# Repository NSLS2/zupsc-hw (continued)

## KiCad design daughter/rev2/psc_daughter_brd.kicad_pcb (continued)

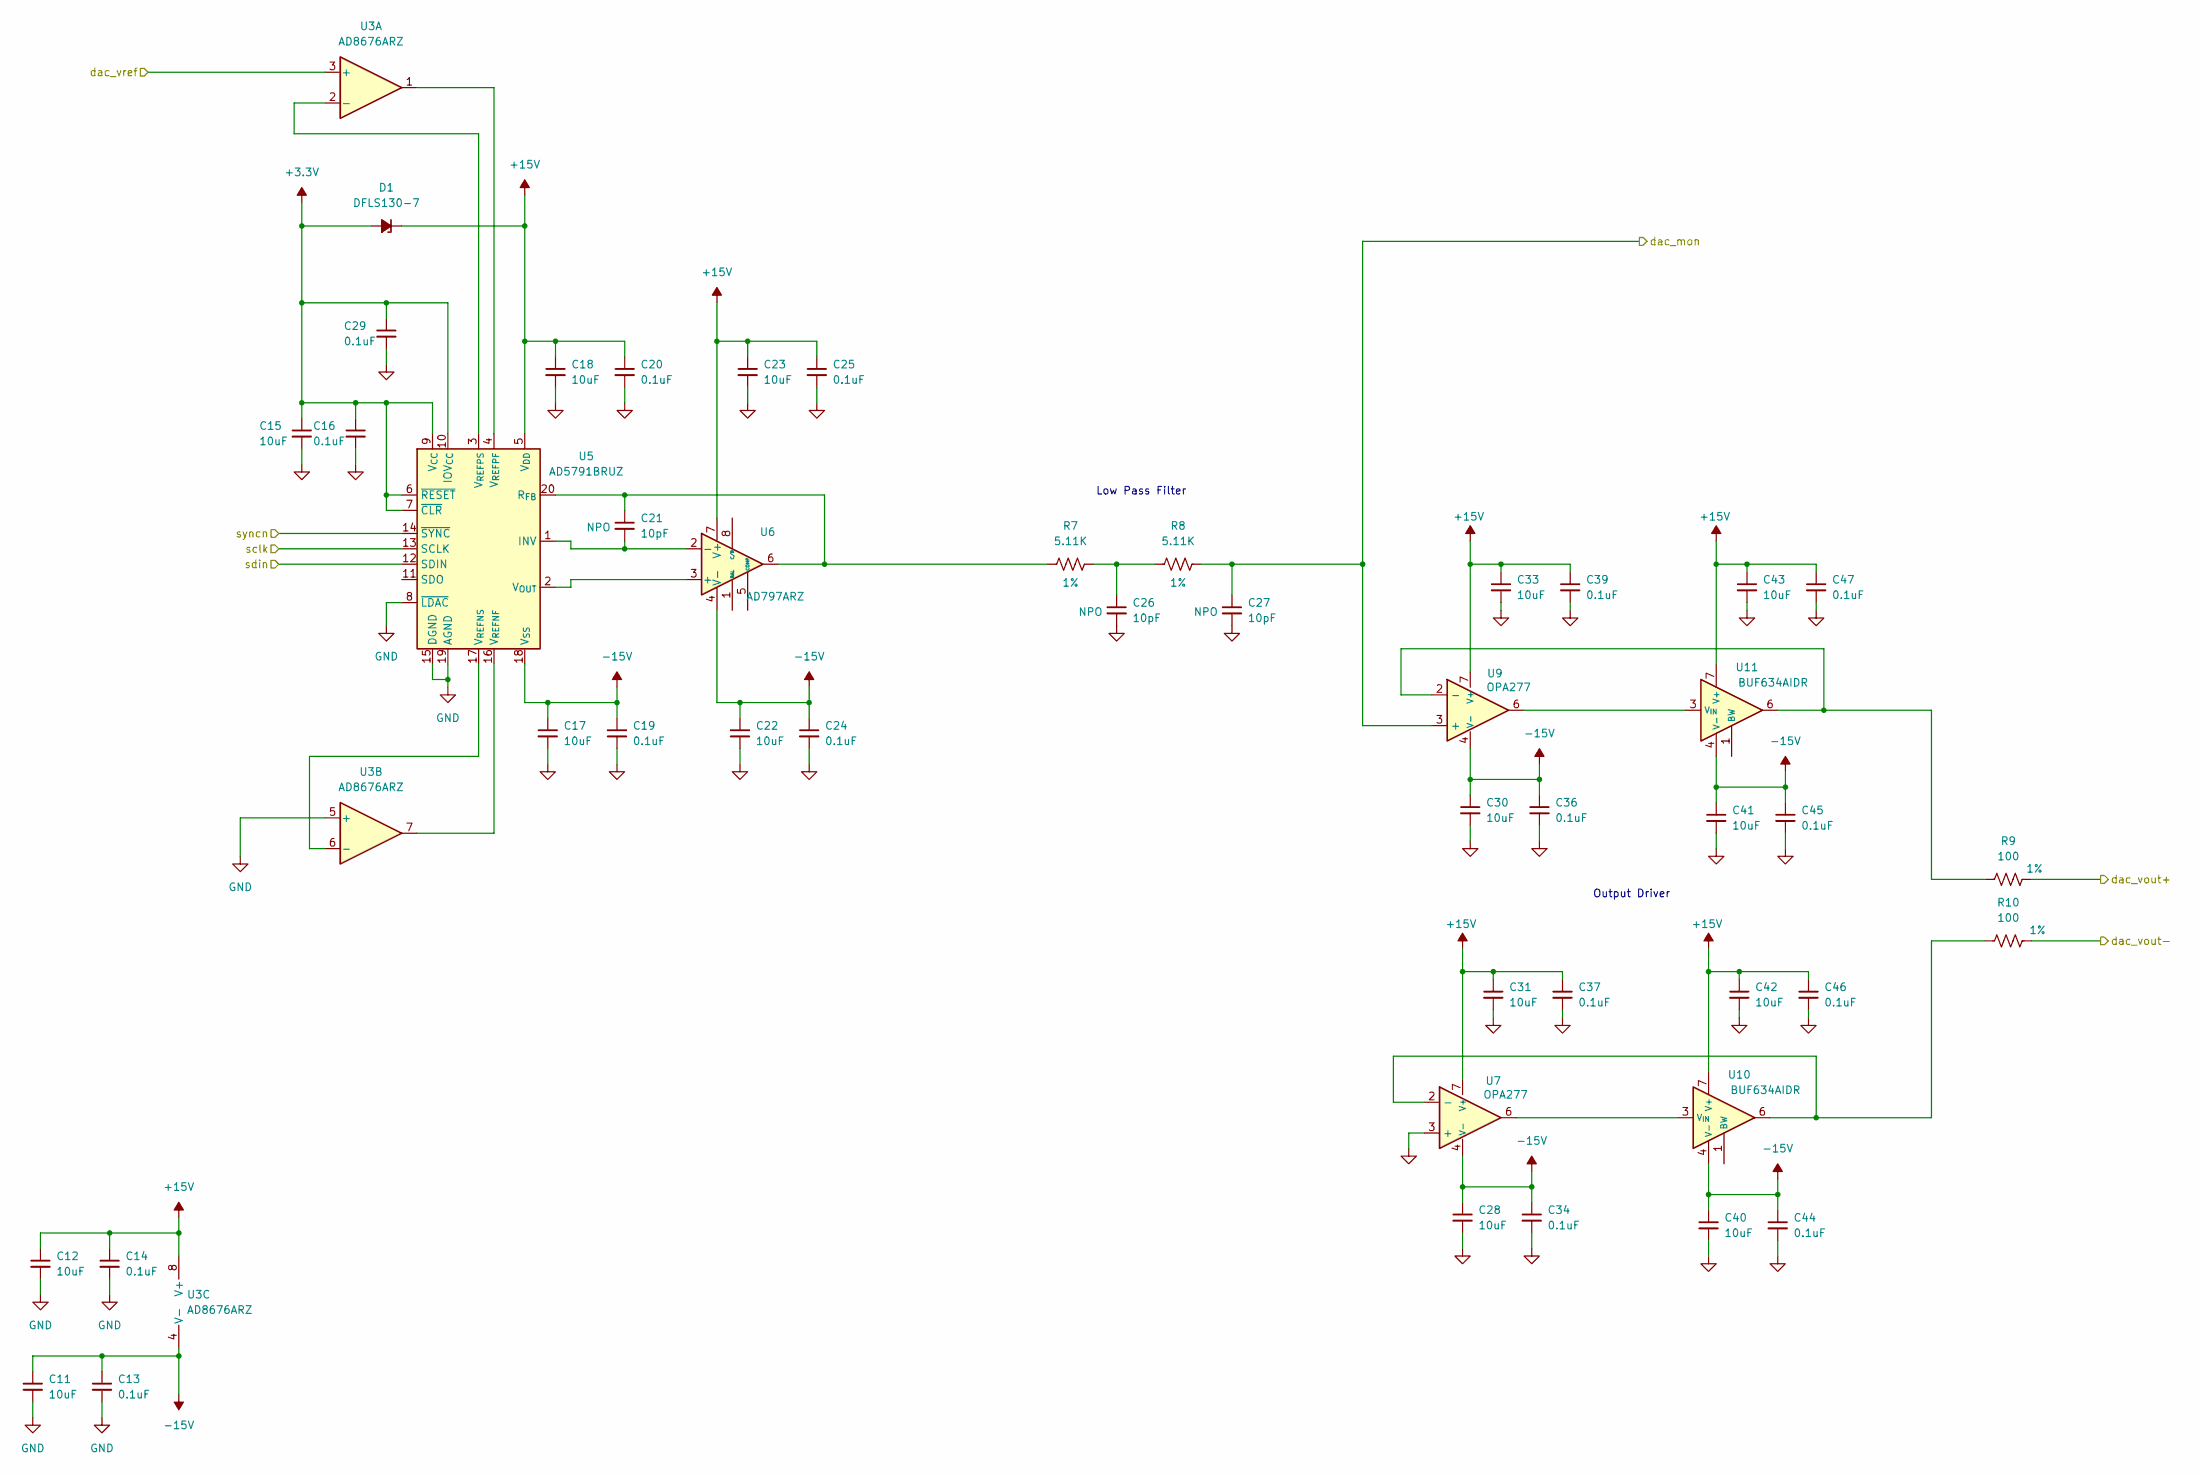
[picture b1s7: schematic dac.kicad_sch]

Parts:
C11, C12, C15, C17, C18, C22, C23, C28, C30, C31, C33, C40, C41, C42, C43: 10uF; C_0603_1608Metric; Voltage 25V; MFG_PN CL10A106MA8NRNC
C13, C14, C16, C19, C20, C24, C25, C29, C34, C36, C37, C39, C44, C45, C46, C47: 0.1uF; C_0402_1005Metric; MFG_PN TMK105BJ104KV-F
C21, C26, C27: 10pF; C_0402_1005Metric; MFG_PN C0402C100K5RACTU
D1: DFLS130-7; DFLS130-7_DIO; MFG_PN DFLS130-7
R7, R8: 5.11K; R_0402_1005Metric; Tolerance 1%; MFG_PN ERJ-2RKF5111X
R9, R10: 100; R_0603_1608Metric; Tolerance 1%; MFG_PN ERJ-2RKF15R0X
U3: AD8676ARZ; SOIC-8_3.9x4.9mm_P1.27mm; MFG_PN AD8676ARZ-REEL7
U5: AD5791BRUZ; TSSOP-20_4.4x6.5mm_P0.65mm; MFG_PN AD5791BRUZ
U6: AD797ARZ; SOIC-8_3.9x4.9mm_P1.27mm; MFG_PN AD797ARZ
U7, U9: OPA277; SOIC-8_3.9x4.9mm_P1.27mm; MFG_PN OPA277UA/2K5
U10, U11: BUF634AIDR; SOIC-8_3.9x4.9mm_P1.27mm; MFG_PN BUF634AIDR

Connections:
+3.3V: C15.1, C16.1, C29.1, D1.2 (A), U5.6 (~RESET), U5.7 (~CLR), U5.9 (V_{CC}), U5.10 (IOV_{CC}); also elsewhere on the board
+15V: C12.1, C14.1, C18.1, C20.1, C23.1, C25.1, C31.1, C33.1, C37.1, C39.1, C42.1, C43.1, C46.1, C47.1, D1.1 (K), U3.8 (V+), U5.5 (V_{DD}), U6.7 (V+), U7.7 (V+), U9.7 (V+), U10.7 (V+), U11.7 (V+); also elsewhere on the board
-15V: C11.1, C13.1, C17.1, C19.1, C22.1, C24.1, C28.1, C30.1, C34.1, C36.1, C40.1, C41.1, C44.1, C45.1, U3.4 (V-), U5.18 (V_{SS}), U6.4 (V-), U7.4 (V-), U9.4 (V-), U10.4 (V-), U11.4 (V-); also elsewhere on the board
/DAC/dac_mon: C27.1, R8.2, U9.3 (+); also elsewhere on the board
/DAC/dac_vout+: R9.2; also elsewhere on the board
/DAC/dac_vout-: R10.2; also elsewhere on the board
/DAC/dac_vref: U3.3 (+); also elsewhere on the board
/DAC/sclk: U5.13 (SCLK); also elsewhere on the board
/DAC/sdin: U5.12 (SDIN); also elsewhere on the board
/DAC/syncn: U5.14 (~SYNC); also elsewhere on the board
GND: C11.2, C12.2, C13.2, C14.2, C15.2, C16.2, C17.2, C18.2, C19.2, C20.2, C22.2, C23.2, C24.2, C25.2, C26.2, C27.2, C28.2, C29.2, C30.2, C31.2, C33.2, C34.2, C36.2, C37.2, C39.2, C40.2, C41.2, C42.2, C43.2, C44.2, C45.2, C46.2, C47.2, U3.5 (+), U5.8 (~LDAC), U5.15 (DGND), U5.19 (AGND), U7.3 (+); also elsewhere on the board
unnamed: C26.1, R7.2, R8.1
unnamed: U3.2 (-), U5.3 (V_{REFPS})
unnamed: U3.6 (-), U5.17 (V_{REFNS})
unnamed: C21.2, U5.1 (INV), U6.2 (-)
unnamed: C21.1, R7.1, U5.20 (R_{FB}), U6.6
unnamed: U5.2 (V_{OUT}), U6.3 (+)
unnamed: U3.7, U5.16 (V_{REFNF})
unnamed: U3.1, U5.4 (V_{REFPF})
unnamed: R10.1, U7.2 (-), U10.6
unnamed: R9.1, U9.2 (-), U11.6
unnamed: U7.6, U10.3 (V_{IN})
unnamed: U9.6, U11.3 (V_{IN})

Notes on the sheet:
Output Driver
Low Pass Filter

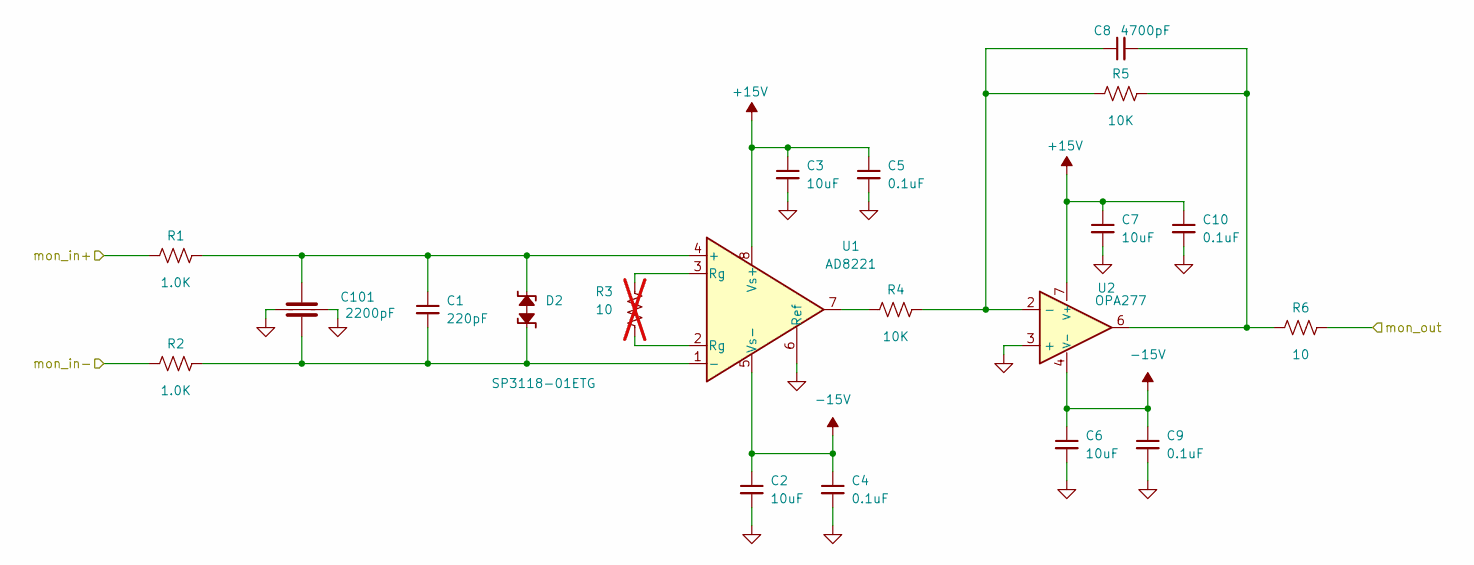
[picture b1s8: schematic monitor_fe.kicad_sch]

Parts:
C1: 220pF; C_0402_1005Metric; MFG_PN C0402C221K5RACTU
C2, C3, C6, C7: 10uF; C_0603_1608Metric; Voltage 25V; MFG_PN CL10A106MA8NRNC
C4, C5, C9, C10: 0.1uF; C_0402_1005Metric; MFG_PN TMK105BJ104KV-F
C8: 4700pF; C_0402_1005Metric; MFG_PN CL05B472KB5NNNC
C101: 2200pF; EMCT101W222M1GV001E; MFG_PN EMCT101W222M1GV001E
D2: SP3118-01ETG; sp3118-01etg; MFG_PN SP3118-01ETG
R1, R2: 1.0K; R_0402_1005Metric; Tolerance 1%; MFG_PN ERJ-2RKF1001X
R3: 10; R_0402_1005Metric; Tolerance 1%; MFG_PN ERJ-2RKF10R0X; not fitted
R4, R5: 10K; R_0402_1005Metric; Tolerance 1%; MFG_PN ERJ-2RKF1002X
R6: 10; R_0402_1005Metric; Tolerance 1%; MFG_PN ERJ-2RKF10R0X
U1: AD8221; SOIC127P600X175-8N; MFG_PN AD8221BRZ
U2: OPA277; SOIC-8_3.9x4.9mm_P1.27mm; MFG_PN OPA277UA/2K5

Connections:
+15V: C3.1, C5.1, C7.1, C10.1, U1.8 (Vs+), U2.7 (V+); also elsewhere on the board
-15V: C2.1, C4.1, C6.1, C9.1, U1.5 (Vs-), U2.4 (V-); also elsewhere on the board
/Monitor ADCs/monitor_ignd+: R1.2; also elsewhere on the board
/Monitor ADCs/monitor_ignd-: R2.2; also elsewhere on the board
/Monitor ADCs/monitor_ignd/mon_out: R6.1; also elsewhere on the board
GND: C2.2, C3.2, C4.2, C5.2, C6.2, C7.2, C9.2, C10.2, C101.3, C101.4, U1.6 (Ref), U2.3 (+); also elsewhere on the board
unnamed: C8.2, R5.1, R6.2, U2.6
unnamed: C1.2, C101.2, D2.1 (A1), R2.1, U1.1 (-)
unnamed: C1.1, C101.1, D2.2 (A2), R1.1, U1.4 (+)
unnamed: R3.1, U1.2 (Rg)
unnamed: R3.2, U1.3 (Rg)
unnamed: R4.2, U1.7
unnamed: C8.1, R4.1, R5.2, U2.2 (-)

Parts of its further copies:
C68, C78, C88: 220pF; C_0402_1005Metric; MFG_PN C0402C221K5RACTU
C69, C70, C73, C74, C79, C80, C83, C84, C89, C90, C93, C94: 10uF; C_0603_1608Metric; Voltage 25V; MFG_PN CL10A106MA8NRNC
C71, C72, C76, C77, C81, C82, C86, C87, C91, C92, C96, C97: 0.1uF; C_0402_1005Metric; MFG_PN TMK105BJ104KV-F
C75, C85, C95: 4700pF; C_0402_1005Metric; MFG_PN CL05B472KB5NNNC
C103, C105, C107: 2200pF; EMCT101W222M1GV001E; MFG_PN EMCT101W222M1GV001E
D3, D6, D7: SP3118-01ETG; sp3118-01etg; MFG_PN SP3118-01ETG
R16, R17, R22, R23, R28, R29: 1.0K; R_0402_1005Metric; Tolerance 1%; MFG_PN ERJ-2RKF1001X
R18, R24, R30: 10; R_0402_1005Metric; Tolerance 1%; MFG_PN ERJ-2RKF10R0X; not fitted
R19, R20, R25, R26, R31, R32: 10K; R_0402_1005Metric; Tolerance 1%; MFG_PN ERJ-2RKF1002X
R21, R27, R33: 10; R_0402_1005Metric; Tolerance 1%; MFG_PN ERJ-2RKF10R0X
U14, U16, U18: AD8221; SOIC127P600X175-8N; MFG_PN AD8221BRZ
U15, U17, U19: OPA277; SOIC-8_3.9x4.9mm_P1.27mm; MFG_PN OPA277UA/2K5

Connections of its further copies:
+15V: C70.1, C72.1, C74.1, C77.1, C80.1, C82.1, C84.1, C87.1, C90.1, C92.1, C94.1, C97.1, U14.8 (Vs+), U15.7 (V+), U16.8 (Vs+), U17.7 (V+), U18.8 (Vs+), U19.7 (V+); also elsewhere on the board
-15V: C69.1, C71.1, C73.1, C76.1, C79.1, C81.1, C83.1, C86.1, C89.1, C91.1, C93.1, C96.1, U14.5 (Vs-), U15.4 (V-), U16.5 (Vs-), U17.4 (V-), U18.5 (Vs-), U19.4 (V-); also elsewhere on the board
/DAC/dac_mon: R16.2; also elsewhere on the board
/Monitor ADCs/monitor_dac/mon_out: R21.1; also elsewhere on the board
/Monitor ADCs/monitor_spare+: R22.2; also elsewhere on the board
/Monitor ADCs/monitor_spare-: R23.2; also elsewhere on the board
/Monitor ADCs/monitor_spare/mon_out: R27.1; also elsewhere on the board
/Monitor ADCs/monitor_vout+: R28.2; also elsewhere on the board
/Monitor ADCs/monitor_vout-: R29.2; also elsewhere on the board
/Monitor ADCs/monitor_vout/mon_out: R33.1; also elsewhere on the board
GND: C69.2, C70.2, C71.2, C72.2, C73.2, C74.2, C76.2, C77.2, C79.2, C80.2, C81.2, C82.2, C83.2, C84.2, C86.2, C87.2, C89.2, C90.2, C91.2, C92.2, C93.2, C94.2, C96.2, C97.2, C103.3, C103.4, C105.3, C105.4, C107.3, C107.4, R17.2, U14.6 (Ref), U15.3 (+), U16.6 (Ref), U17.3 (+), U18.6 (Ref), U19.3 (+); also elsewhere on the board
unnamed: C75.2, R20.1, R21.2, U15.6
unnamed: C85.2, R26.1, R27.2, U17.6
unnamed: C95.2, R32.1, R33.2, U19.6
unnamed: C68.2, C103.2, D3.1 (A1), R17.1, U14.1 (-)
unnamed: C68.1, C103.1, D3.2 (A2), R16.1, U14.4 (+)
unnamed: C78.2, C105.2, D6.1 (A1), R23.1, U16.1 (-)
unnamed: C78.1, C105.1, D6.2 (A2), R22.1, U16.4 (+)
unnamed: C88.2, C107.2, D7.1 (A1), R29.1, U18.1 (-)
unnamed: C88.1, C107.1, D7.2 (A2), R28.1, U18.4 (+)
unnamed: R18.1, U14.2 (Rg)
unnamed: R18.2, U14.3 (Rg)
unnamed: R19.2, U14.7
unnamed: R24.1, U16.2 (Rg)
unnamed: R24.2, U16.3 (Rg)
unnamed: R25.2, U16.7
unnamed: R30.1, U18.2 (Rg)
unnamed: R30.2, U18.3 (Rg)
unnamed: R31.2, U18.7
unnamed: C75.1, R19.1, R20.2, U15.2 (-)
unnamed: C85.1, R25.1, R26.2, U17.2 (-)
unnamed: C95.1, R31.1, R32.2, U19.2 (-)

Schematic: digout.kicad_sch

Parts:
C104, C182, C183, C184, C185, C186: 0.1uF; C_0402_1005Metric; MFG_PN TMK105BJ104KV-F
C187, C188: 10uF; C_0603_1608Metric; Voltage 25V; MFG_PN CL10A106MA8NRNC
CR5, CR6: SP3006-02XTG; SOT563_LTF; MFG_PN SP3006-02XTG
R66, R67, R68, R69: 2.49K; R_0402_1005Metric; Tolerance 1%; MFG_PN ERJ-2RKF2491X
U38: TXUN0104RUTR; PQFP12_RUT_TEX; MFG_PN TXUN0104RUTR
U39, U40: ADUM5240ARZ; R_8_ADI; MFG_PN ADUM5240ARZ

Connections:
+1.8V: C182.1, U38.1 (VCCA); also elsewhere on the board
+5.0V: C104.1, C183.1, C184.1, U38.11 (VCCB), U39.1 (VDD), U40.1 (VDD); also elsewhere on the board
/FPGA connector/dout0: U38.2 (A1); also elsewhere on the board
/FPGA connector/dout1: U38.3 (A2); also elsewhere on the board
/FPGA connector/dout2: U38.4 (A3); also elsewhere on the board
/FPGA connector/dout3: U38.5 (A4); also elsewhere on the board
/Isolated Digital IO/dout0_iso: CR5.1, R66.1, U39.7 (VOA); also elsewhere on the board
/Isolated Digital IO/dout1_iso: CR5.5, R68.1, U39.6 (VOB); also elsewhere on the board
/Isolated Digital IO/dout2_iso: CR6.1, R67.1, U40.7 (VOA); also elsewhere on the board
/Isolated Digital IO/dout3_iso: CR6.5, R69.1, U40.6 (VOB); also elsewhere on the board
/Isolated Digital IO/dout_iso_gnd: CR5.2, CR5.4, CR6.2, CR6.4, U39.5 (GNDISO), U40.5 (GNDISO); also elsewhere on the board
GND: C104.2, C182.2, C183.2, C184.2, C185.2, C186.2, C187.2, C188.2, U38.6 (GND), U38.12 (~OE), U39.4 (GND), U40.4 (GND); also elsewhere on the board
unnamed: U38.10 (B1Y), U39.2 (VIA)
unnamed: U38.9 (B2Y), U39.3 (VIB)
unnamed: U38.8 (B3Y), U40.2 (VIA)
unnamed: U38.7 (B4Y), U40.3 (VIB)
unnamed: C185.1, C187.1, R66.2, R68.2, U39.8 (VISO)
unnamed: C186.1, C188.1, R67.2, R69.2, U40.8 (VISO)

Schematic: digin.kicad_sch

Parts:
C102, C189, C190, C191, C192, C193: 0.1uF; C_0402_1005Metric; MFG_PN TMK105BJ104KV-F
C194, C195: 10uF; C_0603_1608Metric; Voltage 25V; MFG_PN CL10A106MA8NRNC
CR7, CR8: SP3006-02XTG; SOT563_LTF; MFG_PN SP3006-02XTG
R70, R71, R72, R73: 2.49K; R_0402_1005Metric; Tolerance 1%; MFG_PN ERJ-2RKF2491X
U41: TXUN0104RUTR; PQFP12_RUT_TEX; MFG_PN TXUN0104RUTR
U42, U43: ADUM5242ARZ; R_8_ADI; MFG_PN ADUM5242ARZ

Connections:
+1.8V: C189.1, U41.11 (VCCB); also elsewhere on the board
+5.0V: C102.1, C190.1, C191.1, U41.1 (VCCA), U42.1 (VDD), U43.1 (VDD); also elsewhere on the board
/FPGA connector/din0: U41.10 (B1Y); also elsewhere on the board
/FPGA connector/din1: U41.9 (B2Y); also elsewhere on the board
/FPGA connector/din2: U41.8 (B3Y); also elsewhere on the board
/FPGA connector/din3: U41.7 (B4Y); also elsewhere on the board
/Isolated Digital IO/din0_iso: CR7.1, R70.1, U42.7 (VIA); also elsewhere on the board
/Isolated Digital IO/din1_iso: CR7.5, R72.1, U42.6 (VIB); also elsewhere on the board
/Isolated Digital IO/din2_iso: CR8.1, R71.1, U43.7 (VIA); also elsewhere on the board
/Isolated Digital IO/din3_iso: CR8.5, R73.1, U43.6 (VIB); also elsewhere on the board
/Isolated Digital IO/din_iso_gnd: CR7.2, CR7.4, CR8.2, CR8.4, U42.5 (GNDISO), U43.5 (GNDISO); also elsewhere on the board
GND: C102.2, C189.2, C190.2, C191.2, C192.2, C193.2, C194.2, C195.2, U41.6 (GND), U41.12 (~OE), U42.4 (GND), U43.4 (GND); also elsewhere on the board
unnamed: U41.2 (A1), U42.2 (VOA)
unnamed: U41.3 (A2), U42.3 (VOB)
unnamed: U41.4 (A3), U43.2 (VOA)
unnamed: U41.5 (A4), U43.3 (VOB)
unnamed: C192.1, C194.1, R70.2, R72.2, U42.8 (VISO)
unnamed: C193.1, C195.1, R71.2, R73.2, U43.8 (VISO)

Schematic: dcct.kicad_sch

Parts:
C35: 2200pF; EMCT101W222M1GV001E; MFG_PN EMCT101W222M1GV001E
C109: 3nF; C_0603_1608Metric; MFG_PN C0603C302J5GACTU
C111: 2nF; C_0603_1608Metric; MFG_PN C0603C202F5GACTU
C113, C137, C149, C150, C152, C158, C165, C175, C179, C181: 0.1uF; C_0402_1005Metric; MFG_PN TMK105BJ104KV-F
C114, C136, C139, C154, C156, C161, C162, C178, C180: 10uF; C_0603_1608Metric; Voltage 25V; MFG_PN CL10A106MA8NRNC
C120, C122: 470pF; C_0402_1005Metric; MFG_PN GRM1555C1H471FA01D
C138, C177: 6800pF; C_0402_1005Metric; MFG_PN CL05B682KB5NNNC
C151, C176: 3300pF; C_0402_1005Metric; MFG_PN CL05B332KB5NNNC
D4: SP3118-01ETG; sp3118-01etg; MFG_PN SP3118-01ETG
D8: BAT54S; SOT-23; MFG_PN BAT54S
R37, R39, R40, R45, R47, R51, R62, R77: 10.0K; R_0603_1608Metric; Tolerance 0.1%; MFG_PN RT0603BRB0710KL
R54, R55: 1.0K; R_0402_1005Metric; Tolerance 1%; MFG_PN ERJ-2RKF1001X
R56: 665; R_0603_1608Metric; MFG_PN RQ73C1J665RBTD
R64, R65: 30.1; R_0402_1005Metric; Tolerance 1%; MFG_PN ERJ-2RKF30R1X
R85: 665; R_0603_1608Metric; MFG_PN RQ73C1J665RBTD; not fitted
U4: AD8676xR; SOIC-8_3.9x4.9mm_P1.27mm; MFG_PN AD8676BRZ
U21: THP210DR; SOIC_210DR_TEX; MFG_PN THP210DR
U33: AD8429BRZ; SOIC127P600X175-8N; MFG_PN AD8429BRZ
U37: LTC2376CDE-20; DFN-16_DE_LIT; MFG_PN LTC2376CDE-20#PBF

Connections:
+1.8V: C180.1, C181.1, U37.15 (OVDD); also elsewhere on the board
+2.5V: C178.1, C179.1, U37.2 (VDD); also elsewhere on the board
+5.3VA: C136.1, C137.1, C162.1, C165.1, D8.2 (K), U4.8 (V+), U21.3 (VS+), U21.7 (PD*); also elsewhere on the board
+15V: C156.1, C158.1, U33.8 (Vs+); also elsewhere on the board
-5.3VA: C113.1, C114.1, C139.1, C149.1, D8.1 (A), U4.4 (V-), U21.6 (VS-); also elsewhere on the board
-15V: C152.1, C154.1, U33.5 (Vs-); also elsewhere on the board
/DCCT ADCs/DCCT Channel 1/drv_vref: C150.1, U21.2 (VOCM); also elsewhere on the board
/DCCT ADCs/adc_vref: C161.1, C175.1, U37.7 (REF), U37.8 (REF/*DGC); also elsewhere on the board
/DCCT ADCs/dcct0+: R55.2; also elsewhere on the board
/DCCT ADCs/dcct0-: R54.2; also elsewhere on the board
/DCCT ADCs/dcct0_sdo: U37.14 (SDO); also elsewhere on the board
/DCCT ADCs/dcct_busy: U37.11 (BUSY); also elsewhere on the board
/DCCT ADCs/dcct_cnv: U37.9 (CNV); also elsewhere on the board
/DCCT ADCs/dcct_sck: U37.13 (SCK); also elsewhere on the board
GND: C35.3, C35.4, C113.2, C114.2, C136.2, C137.2, C138.1, C139.2, C149.2, C150.2, C152.2, C154.2, C156.2, C158.2, C161.2, C162.2, C165.2, C175.2, C177.2, C178.2, C179.2, C180.2, C181.2, R51.2, U4.3 (+), U4.5 (+), U33.6 (Ref), U37.1 (CHAIN), U37.3 (GND), U37.6 (GND), U37.10 (GND), U37.12 (RDL/SDI), U37.16 (GND), U37.17 (GND); also elsewhere on the board
unnamed: C109.2, R37.1, R39.2, U4.1
unnamed: C111.2, R40.1, R45.2, U4.7
unnamed: C35.2, C151.2, D4.1 (A1), R55.1, U33.4 (+)
unnamed: C35.1, C151.1, D4.2 (A2), R54.1, U33.1 (-)
unnamed: D8.3 (COM), R77.2, U33.7
unnamed: R56.1, R85.1, U33.2 (Rg)
unnamed: R56.2, R85.2, U33.3 (Rg)
unnamed: C109.1, R37.2, R77.1, U4.2 (-)
unnamed: C111.1, R39.1, R40.2, U4.6 (-)
unnamed: C120.1, R45.1, R47.2, U21.8 (IN+)
unnamed: C122.2, R51.1, R62.2, U21.1 (IN-)
unnamed: C122.1, R62.1, R65.2, U21.4 (OUT+)
unnamed: C120.2, R47.1, R64.2, U21.5 (OUT-)
unnamed: C138.2, C176.1, R64.1, U37.4 (IN+)
unnamed: C176.2, C177.1, R65.1, U37.5 (IN-)

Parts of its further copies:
C38: 2200pF; EMCT101W222M1GV001E; MFG_PN EMCT101W222M1GV001E
C110: 3nF; C_0603_1608Metric; MFG_PN C0603C302J5GACTU
C112: 2nF; C_0603_1608Metric; MFG_PN C0603C202F5GACTU
C115, C117, C123, C130, C144, C146, C159, C173, C174, C196: 0.1uF; C_0402_1005Metric; MFG_PN TMK105BJ104KV-F
C116, C141: 3300pF; C_0402_1005Metric; MFG_PN CL05B332KB5NNNC
C118, C119, C121, C127, C143, C145, C169, C171, C172: 10uF; C_0603_1608Metric; Voltage 25V; MFG_PN CL10A106MA8NRNC
C128, C129: 470pF; C_0402_1005Metric; MFG_PN GRM1555C1H471FA01D
C140, C142: 6800pF; C_0402_1005Metric; MFG_PN CL05B682KB5NNNC
D5: SP3118-01ETG; sp3118-01etg; MFG_PN SP3118-01ETG
D9: BAT54S; SOT-23; MFG_PN BAT54S
R35, R38, R41, R44, R46, R48, R58, R63: 10.0K; R_0603_1608Metric; Tolerance 0.1%; MFG_PN RT0603BRB0710KL
R36: 665; R_0603_1608Metric; MFG_PN RQ73C1J665RBTD
R42, R43: 1.0K; R_0402_1005Metric; Tolerance 1%; MFG_PN ERJ-2RKF1001X
R52, R53: 30.1; R_0402_1005Metric; Tolerance 1%; MFG_PN ERJ-2RKF30R1X
R86: 665; R_0603_1608Metric; MFG_PN RQ73C1J665RBTD; not fitted
U8: AD8676xR; SOIC-8_3.9x4.9mm_P1.27mm; MFG_PN AD8676BRZ
U26: THP210DR; SOIC_210DR_TEX; MFG_PN THP210DR
U27: AD8429BRZ; SOIC127P600X175-8N; MFG_PN AD8429BRZ
U31: LTC2376CDE-20; DFN-16_DE_LIT; MFG_PN LTC2376CDE-20#PBF

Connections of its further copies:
+1.8V: C145.1, C146.1, U31.15 (OVDD); also elsewhere on the board
+2.5V: C143.1, C144.1, U31.2 (VDD); also elsewhere on the board
+5.3VA: C127.1, C130.1, C171.1, C173.1, D9.2 (K), U8.8 (V+), U26.3 (VS+), U26.7 (PD*); also elsewhere on the board
+15V: C121.1, C123.1, U27.8 (Vs+); also elsewhere on the board
-5.3VA: C115.1, C118.1, C172.1, C174.1, D9.1 (A), U8.4 (V-), U26.6 (VS-); also elsewhere on the board
-15V: C117.1, C119.1, U27.5 (Vs-); also elsewhere on the board
/DCCT ADCs/DCCT Channel 1/drv_vref: C159.1, U26.2 (VOCM); also elsewhere on the board
/DCCT ADCs/DCCT Channel 2/busy: U31.11 (BUSY)
/DCCT ADCs/adc_vref: C169.1, C196.1, U31.7 (REF), U31.8 (REF/*DGC); also elsewhere on the board
/DCCT ADCs/dcct1+: R43.2; also elsewhere on the board
/DCCT ADCs/dcct1-: R42.2; also elsewhere on the board
/DCCT ADCs/dcct1_sdo: U31.14 (SDO); also elsewhere on the board
/DCCT ADCs/dcct_cnv: U31.9 (CNV); also elsewhere on the board
/DCCT ADCs/dcct_sck: U31.13 (SCK); also elsewhere on the board
GND: C38.3, C38.4, C115.2, C117.2, C118.2, C119.2, C121.2, C123.2, C127.2, C130.2, C140.1, C142.2, C143.2, C144.2, C145.2, C146.2, C159.2, C169.2, C171.2, C172.2, C173.2, C174.2, C196.2, R58.2, U8.3 (+), U8.5 (+), U27.6 (Ref), U31.1 (CHAIN), U31.3 (GND), U31.6 (GND), U31.10 (GND), U31.12 (RDL/SDI), U31.16 (GND), U31.17 (GND); also elsewhere on the board
unnamed: C110.2, R38.1, R41.2, U8.1
unnamed: C112.2, R44.1, R46.2, U8.7
unnamed: C38.2, C116.2, D5.1 (A1), R43.1, U27.4 (+)
unnamed: C38.1, C116.1, D5.2 (A2), R42.1, U27.1 (-)
unnamed: D9.3 (COM), R35.2, U27.7
unnamed: R36.1, R86.1, U27.2 (Rg)
unnamed: R36.2, R86.2, U27.3 (Rg)
unnamed: C110.1, R35.1, R38.2, U8.2 (-)
unnamed: C112.1, R41.1, R44.2, U8.6 (-)
unnamed: C128.1, R46.1, R48.2, U26.8 (IN+)
unnamed: C129.2, R58.1, R63.2, U26.1 (IN-)
unnamed: C129.1, R53.2, R63.1, U26.4 (OUT+)
unnamed: C128.2, R48.1, R52.2, U26.5 (OUT-)
unnamed: C140.2, C141.1, R52.1, U31.4 (IN+)
unnamed: C141.2, C142.1, R53.1, U31.5 (IN-)

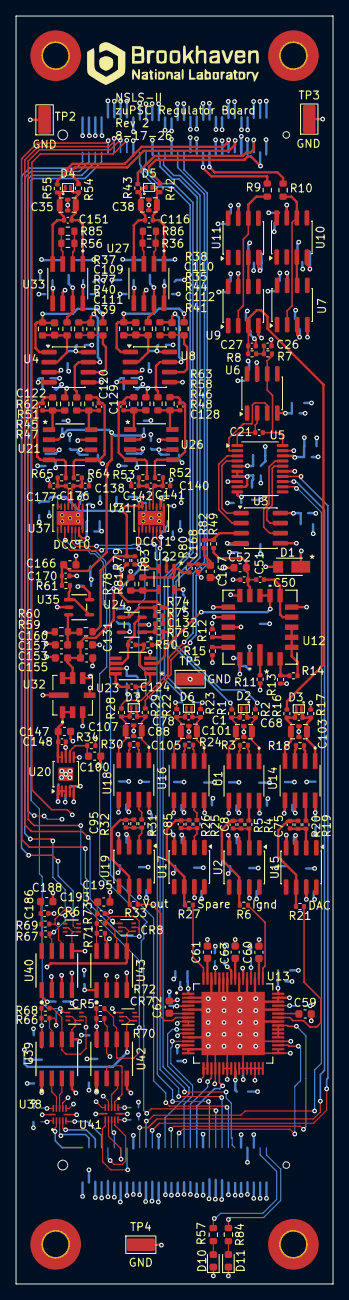
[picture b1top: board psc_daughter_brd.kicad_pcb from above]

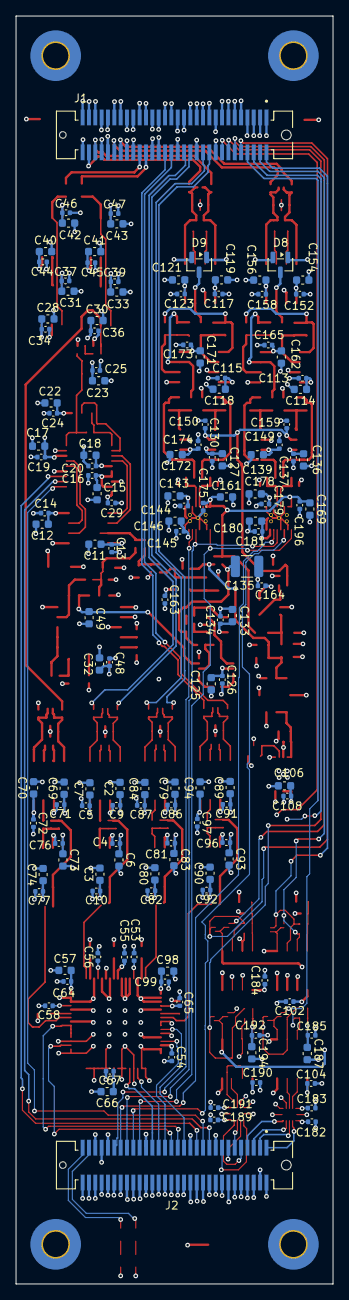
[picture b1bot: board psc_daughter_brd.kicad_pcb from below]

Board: 10 copper layers, 40.0 x 160.0 mm, 344 parts (141 on the bottom side), 176 nets.

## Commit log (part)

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2026-03-28 Add Readme
2026-03-28 Add board picture
2026-03-28 Tweak readme
2026-03-28 Edit board picture
2026-03-28 Edit Readme
2026-03-28 Add KiCad files
